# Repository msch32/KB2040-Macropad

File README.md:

# KB2040-Macropad
Small Macropad to extend a TKL Keyboard with a numbad for blender, etc. Can also be used as a general purpose macropad

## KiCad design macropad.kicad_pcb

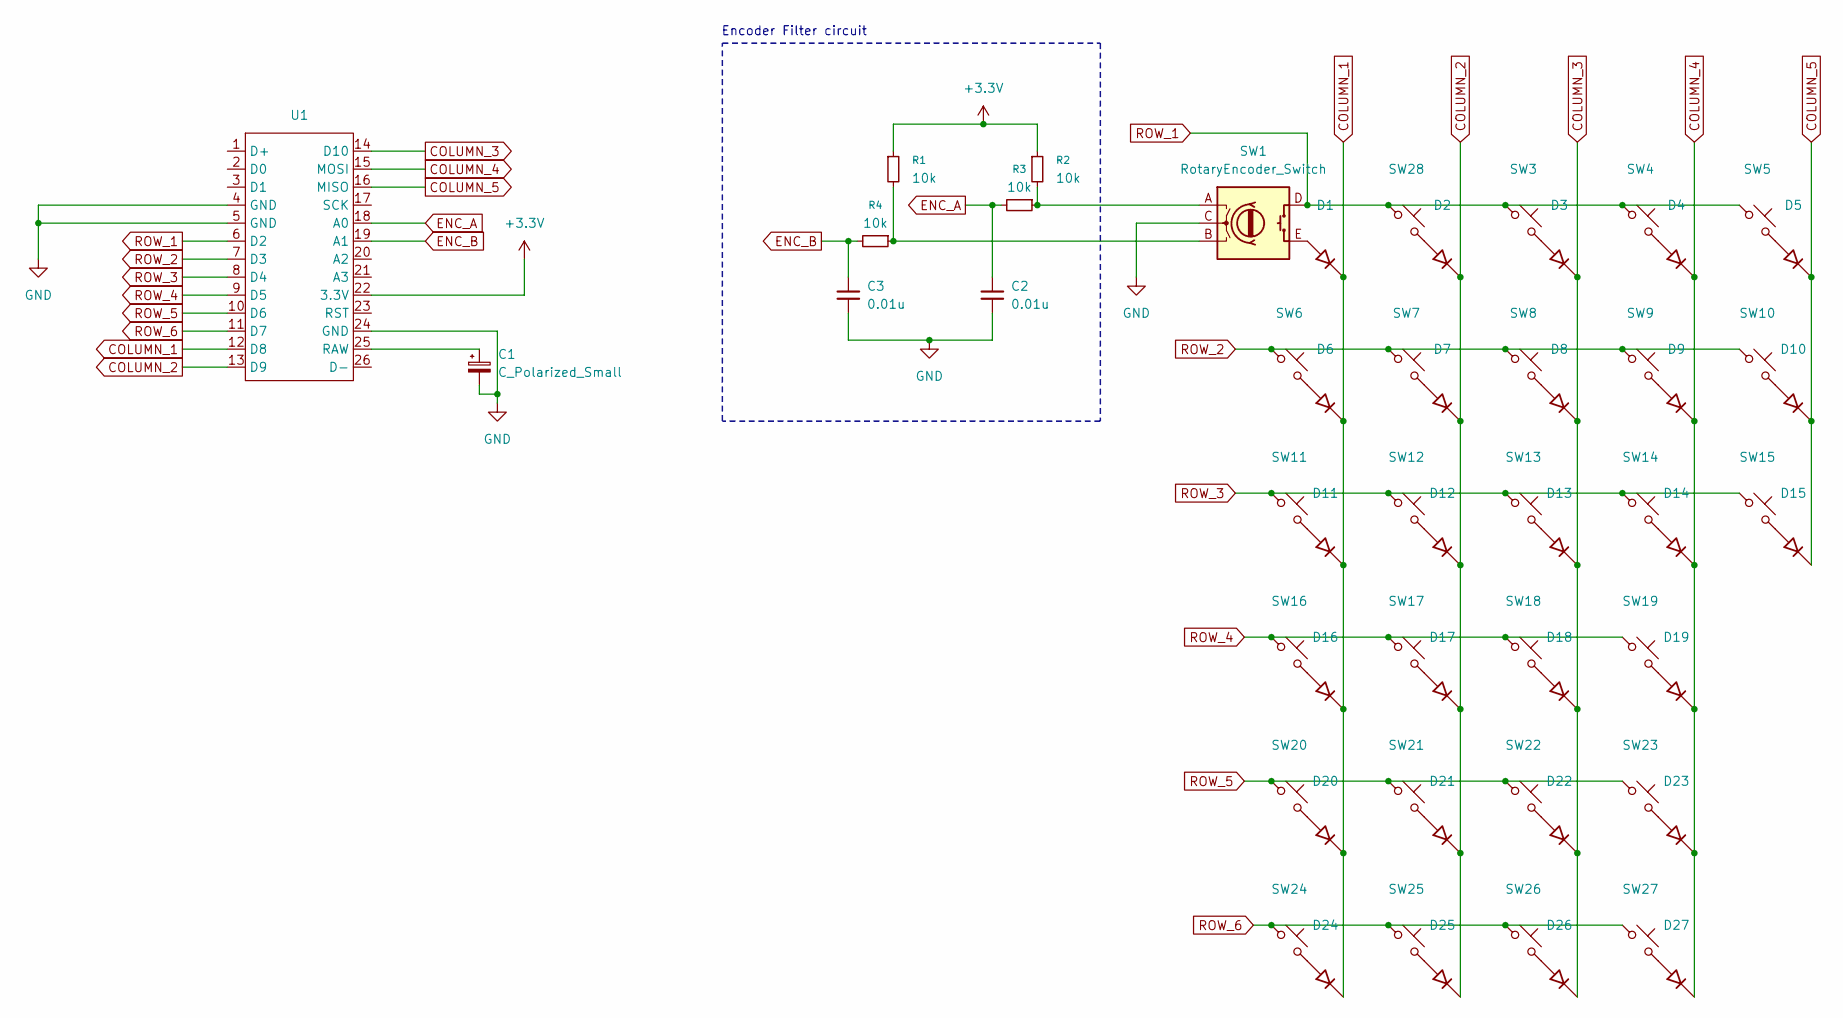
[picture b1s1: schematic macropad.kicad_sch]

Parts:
C1: C_Polarized_Small; Cap_SMD_WE; Digikey 732-8419-1-ND
C2, C3: 0.01u; C_0201_0603Metric_Pad0.64x0.40mm_HandSolder
D1, D2, D3, D4, D5, D6, D7, D8, D9, D10, D11, D12, D13, D14, D15, D16, D17, D18, D19, D20, D21, D22, D23, D24, D25, D26, D27: 1N4148WS-7-F; D_SOD-323; Digikey 1N4148WS-FDICT-ND
R1, R2, R3, R4: 10k; R_0603_1608Metric_Pad0.98x0.95mm_HandSolder
SW1: RotaryEncoder_Switch; PEC11S-929F-S0015; Digikey 118-PEC11S-929F-S0015-ND
SW3, SW4, SW5, SW6, SW7, SW8, SW9, SW10, SW11, SW12, SW13, SW14, SW16, SW17, SW18, SW19, SW20, SW21, SW22, SW23, SW24, SW26, SW28: SW_Push_45deg; SW_Cherry_MX_PCB_1.00u
SW15, SW27: SW_Push_45deg; SW_Cherry_MX_2.00u_Vertical_PCB
SW25: SW_Push_45deg; SW_Cherry_MX_2.00u_PCB
U1: KB2040

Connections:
+3.3V: R1.1, R2.1, U1.22 (3.3V)
COLUMN_1: D1.1 (K), D6.1 (K), D11.1 (K), D16.1 (K), D20.1 (K), D24.1 (K), U1.12 (D8)
COLUMN_2: D2.1 (K), D7.1 (K), D12.1 (K), D17.1 (K), D21.1 (K), D25.1 (K), U1.13 (D9)
COLUMN_3: D3.1 (K), D8.1 (K), D13.1 (K), D18.1 (K), D22.1 (K), D26.1 (K), U1.14 (D10)
COLUMN_4: D4.1 (K), D9.1 (K), D14.1 (K), D19.1 (K), D23.1 (K), D27.1 (K), U1.15 (MOSI)
COLUMN_5: D5.1 (K), D10.1 (K), D15.1 (K), U1.16 (MISO)
ENC_A: C2.1, R3.2, U1.18 (A0)
ENC_B: C3.1, R4.2, U1.19 (A1)
GND: C1.2, C2.2, C3.2, SW1.C, U1.4 (GND), U1.5 (GND), U1.24 (GND)
unnamed: D1.2 (A), SW1.E
unnamed: D2.2 (A), SW28.2
unnamed: D3.2 (A), SW3.2
unnamed: D4.2 (A), SW4.2
unnamed: D5.2 (A), SW5.2
unnamed: D6.2 (A), SW6.2
unnamed: D7.2 (A), SW7.2
unnamed: D8.2 (A), SW8.2
unnamed: D9.2 (A), SW9.2
unnamed: D10.2 (A), SW10.2
unnamed: D11.2 (A), SW11.2
unnamed: D12.2 (A), SW12.2
unnamed: D13.2 (A), SW13.2
unnamed: D14.2 (A), SW14.2
unnamed: D15.2 (A), SW15.2
unnamed: D16.2 (A), SW16.2
unnamed: D17.2 (A), SW17.2
unnamed: D18.2 (A), SW18.2
unnamed: D19.2 (A), SW19.2
unnamed: D20.2 (A), SW20.2
unnamed: D21.2 (A), SW21.2
unnamed: D22.2 (A), SW22.2
unnamed: D23.2 (A), SW23.2
unnamed: D24.2 (A), SW24.2
unnamed: D25.2 (A), SW25.2
unnamed: D26.2 (A), SW26.2
unnamed: D27.2 (A), SW27.2
unnamed: R1.2, R4.1, SW1.B
unnamed: R2.2, R3.1, SW1.A
unnamed: C1.1, U1.25 (RAW)
ROW_1: SW1.D, SW3.1, SW4.1, SW5.1, SW28.1, U1.6 (D2)
ROW_2: SW6.1, SW7.1, SW8.1, SW9.1, SW10.1, U1.7 (D3)
ROW_3: SW11.1, SW12.1, SW13.1, SW14.1, SW15.1, U1.8 (D4)
ROW_4: SW16.1, SW17.1, SW18.1, SW19.1, U1.9 (D5)
ROW_5: SW20.1, SW21.1, SW22.1, SW23.1, U1.10 (D6)
ROW_6: SW24.1, SW25.1, SW26.1, SW27.1, U1.11 (D7)

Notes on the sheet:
Encoder Filter circuit

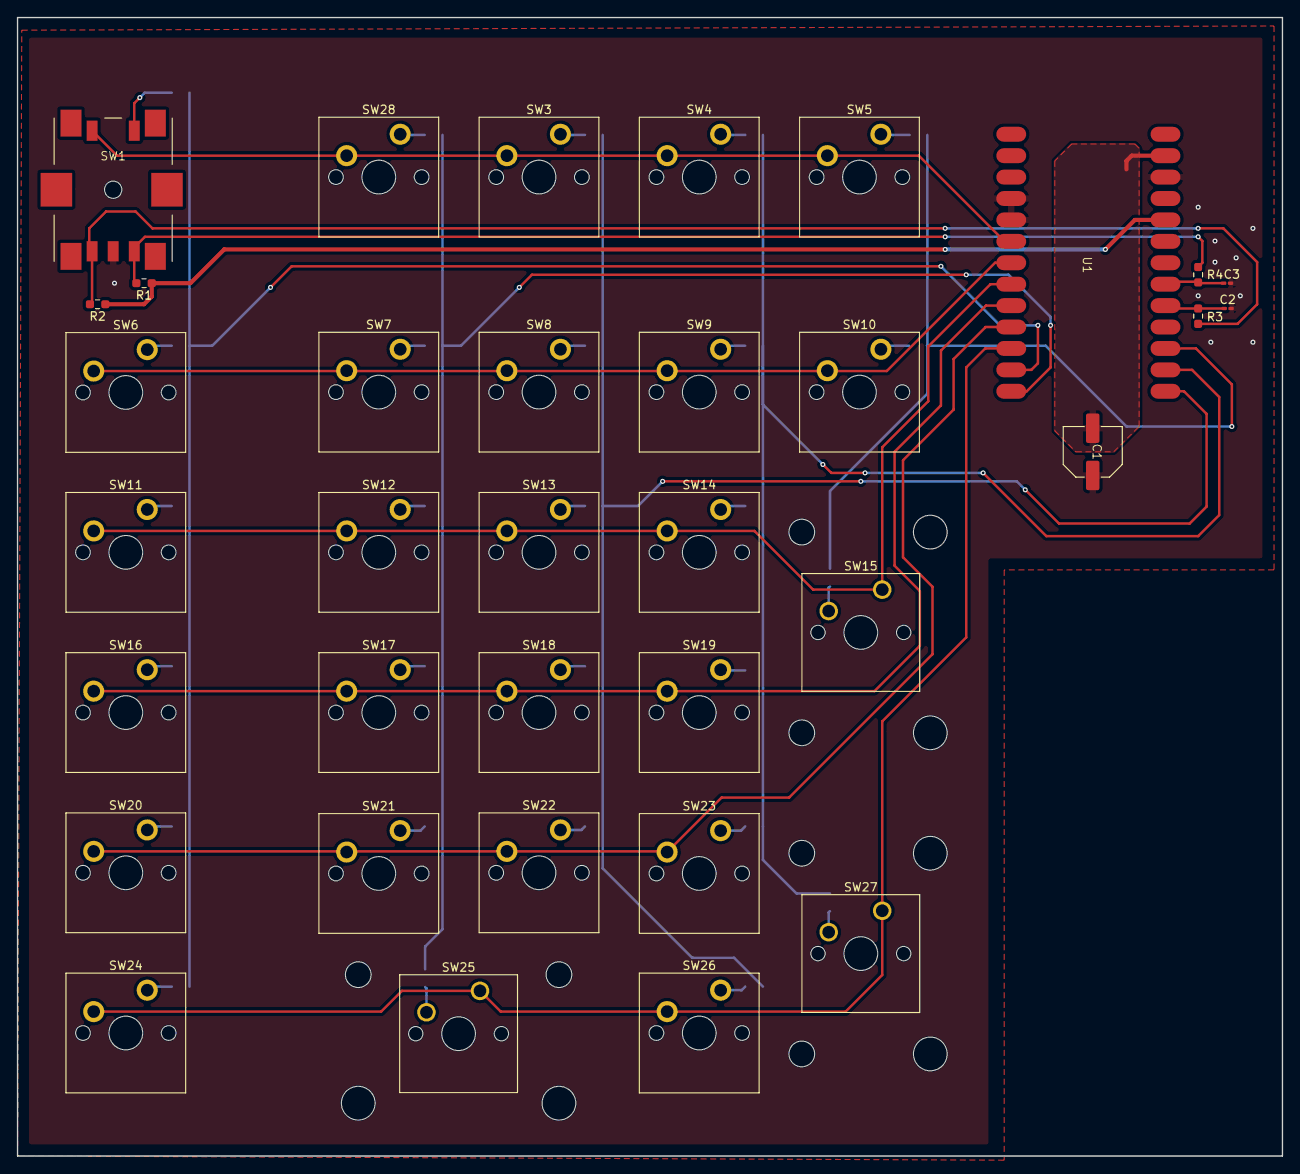
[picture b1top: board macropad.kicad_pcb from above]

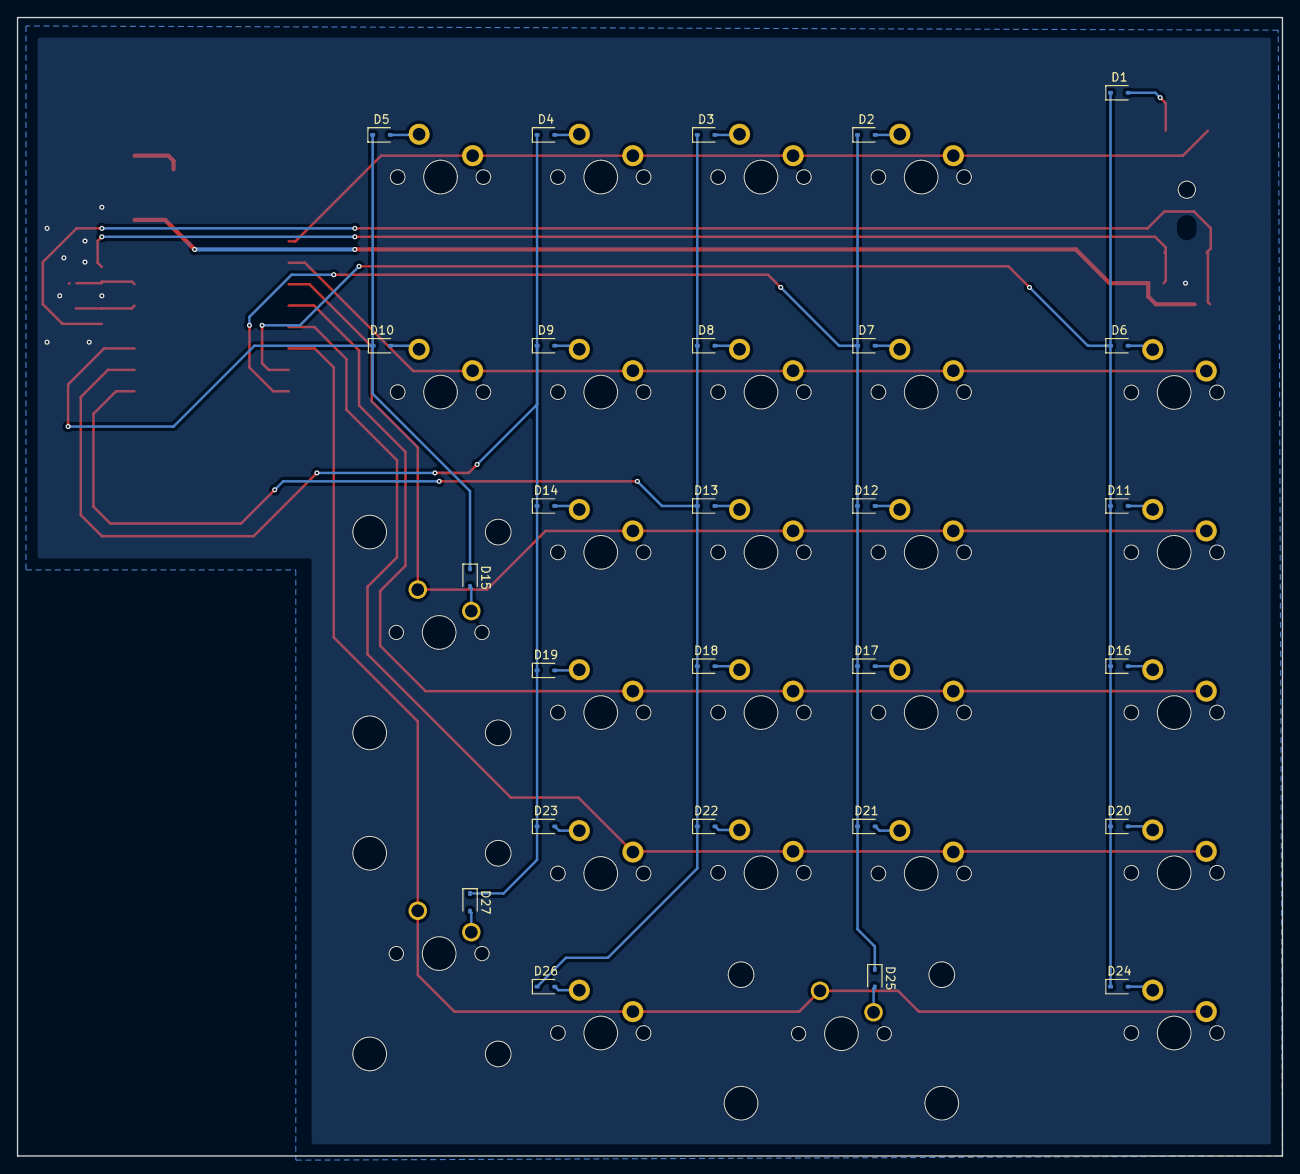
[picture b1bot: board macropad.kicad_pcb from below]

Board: 2 copper layers, 150.0 x 135.0 mm, 62 parts (27 on the bottom side), 45 nets.
